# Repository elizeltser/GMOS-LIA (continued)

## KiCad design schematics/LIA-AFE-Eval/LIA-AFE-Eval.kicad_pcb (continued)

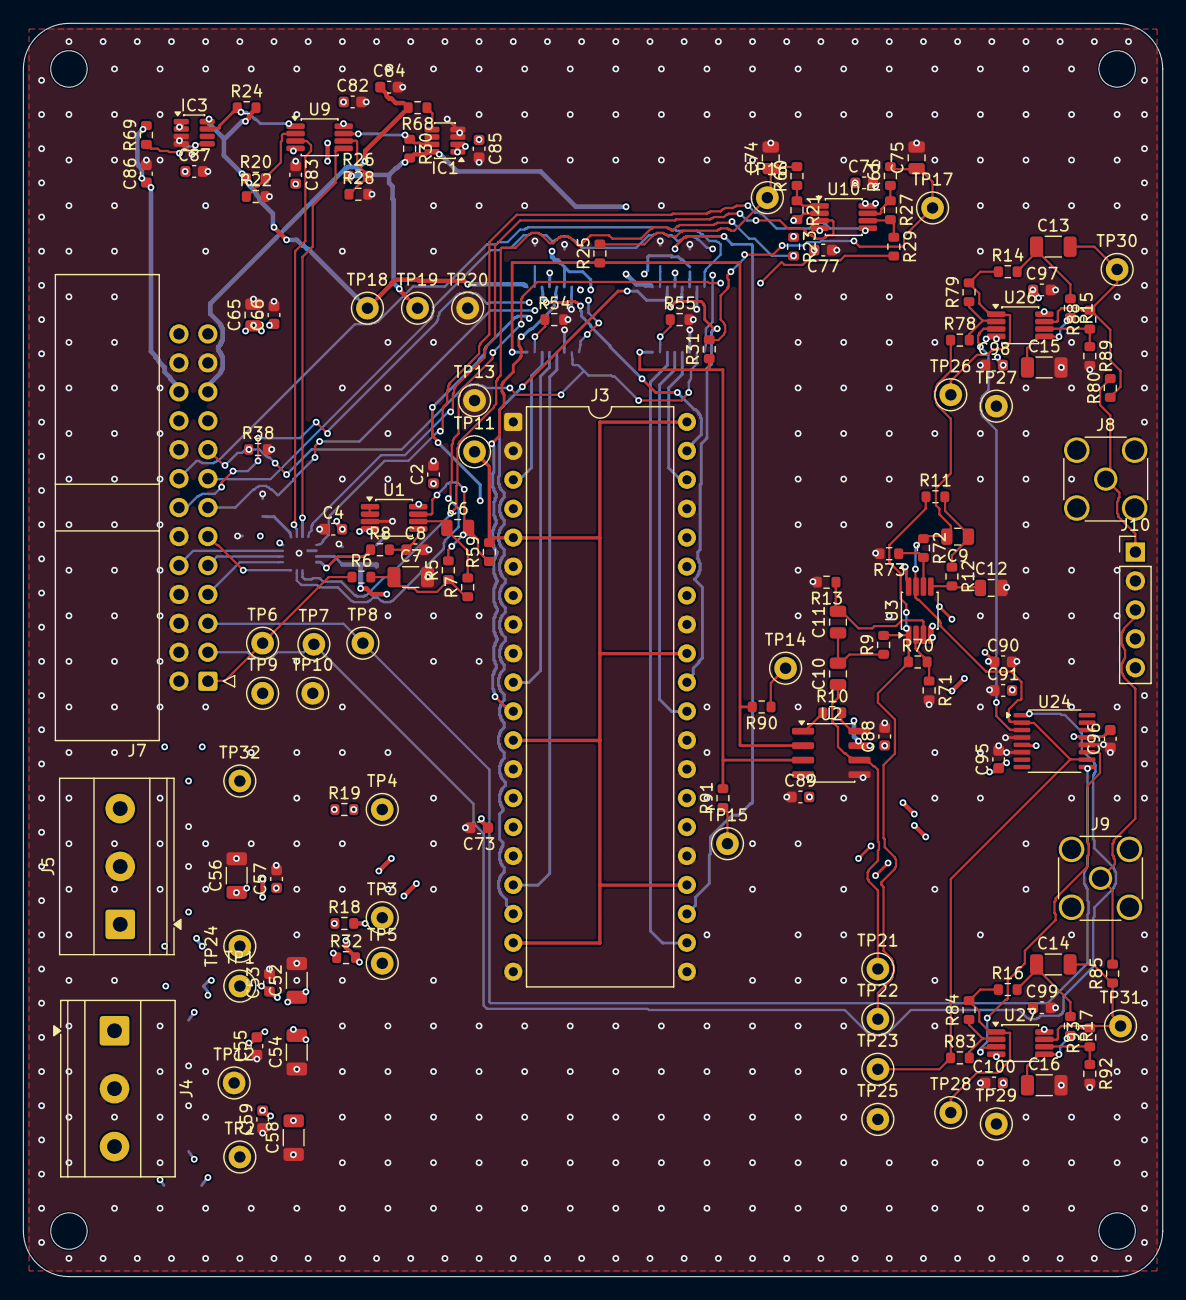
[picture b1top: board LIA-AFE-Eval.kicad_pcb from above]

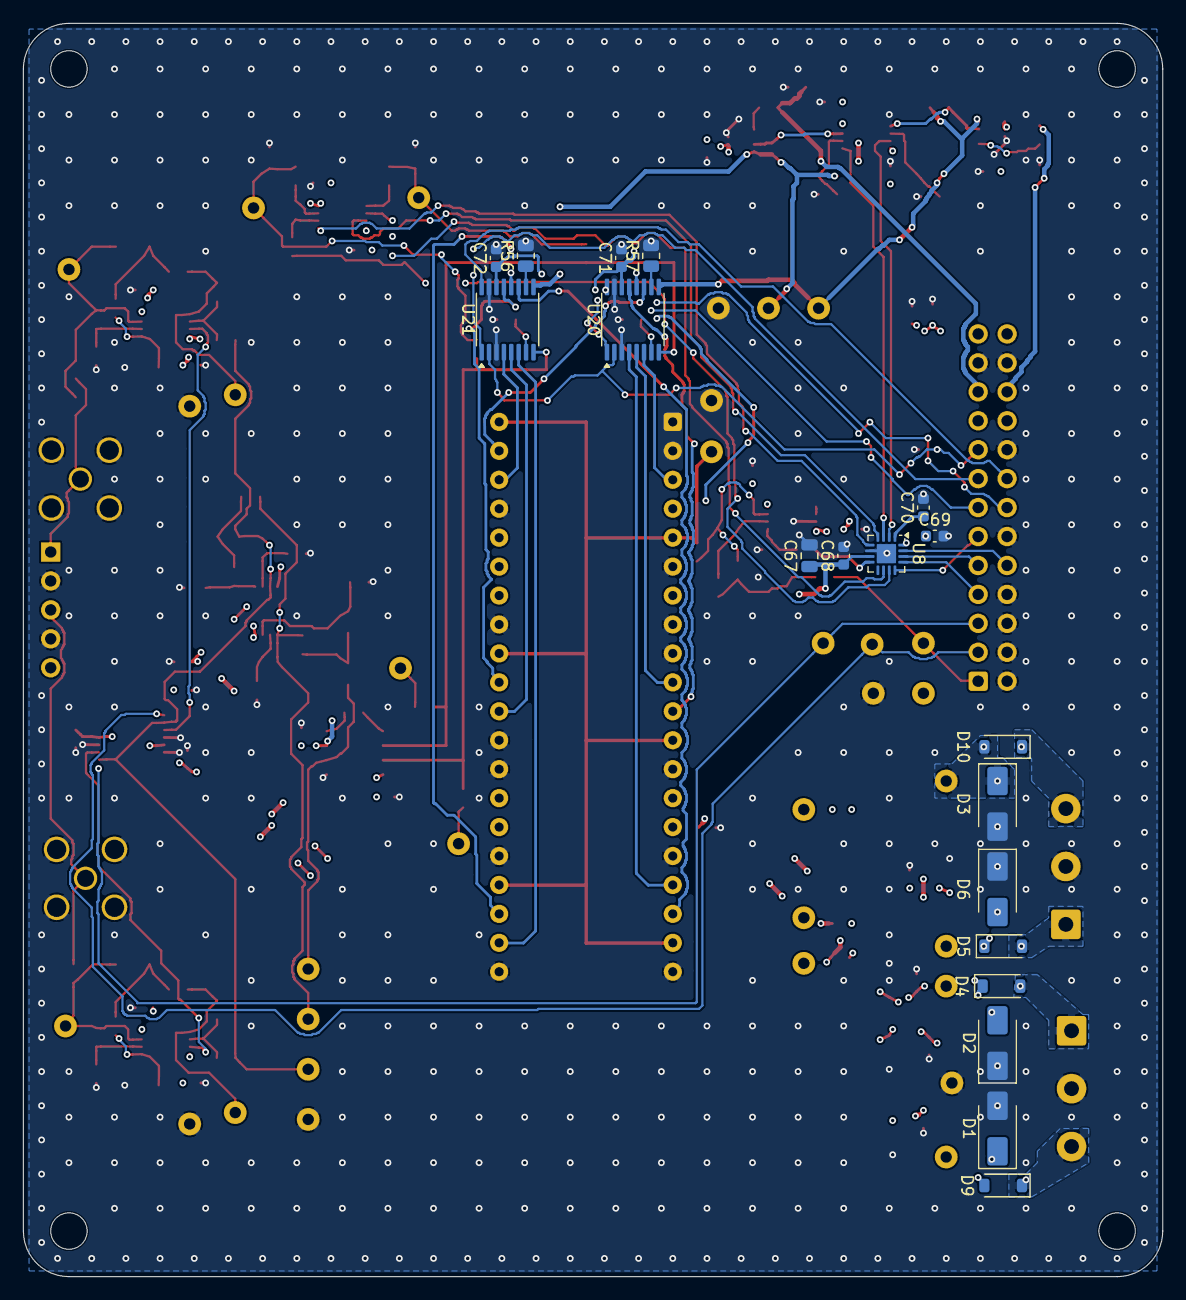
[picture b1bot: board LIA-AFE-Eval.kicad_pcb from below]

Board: 4 copper layers, 100.0 x 110.0 mm, 168 parts (19 on the bottom side), 102 nets.

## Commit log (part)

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2025-07-14 Updated TreeTTester and more
2025-07-19 Major update on LIASetup
2025-07-19 fixed VITester - now passes basic tests
2025-07-22 not sure what changed but OK
2025-07-23 changes from lab
2025-12-25 extensive cleanup
2025-12-27 Major cleanup, upload of STM project
2025-12-27 now it can also flash the mcu
2026-01-07 MCP changes, running well
2026-02-19 save changes - then redo all
2026-02-21 Redo of many things - now FSD centered
2026-03-07 Implement most of the tests - not tested yet
2026-04-05 This is a commit for adding "readout.tex" and its compilation to the repository for specific file Yeal required.
2026-04-11 moved to thesis folder name, intro grows larger, claude.md splitted
2026-04-22 matching transistors page
2026-04-24 lia tests for optimization of phase
